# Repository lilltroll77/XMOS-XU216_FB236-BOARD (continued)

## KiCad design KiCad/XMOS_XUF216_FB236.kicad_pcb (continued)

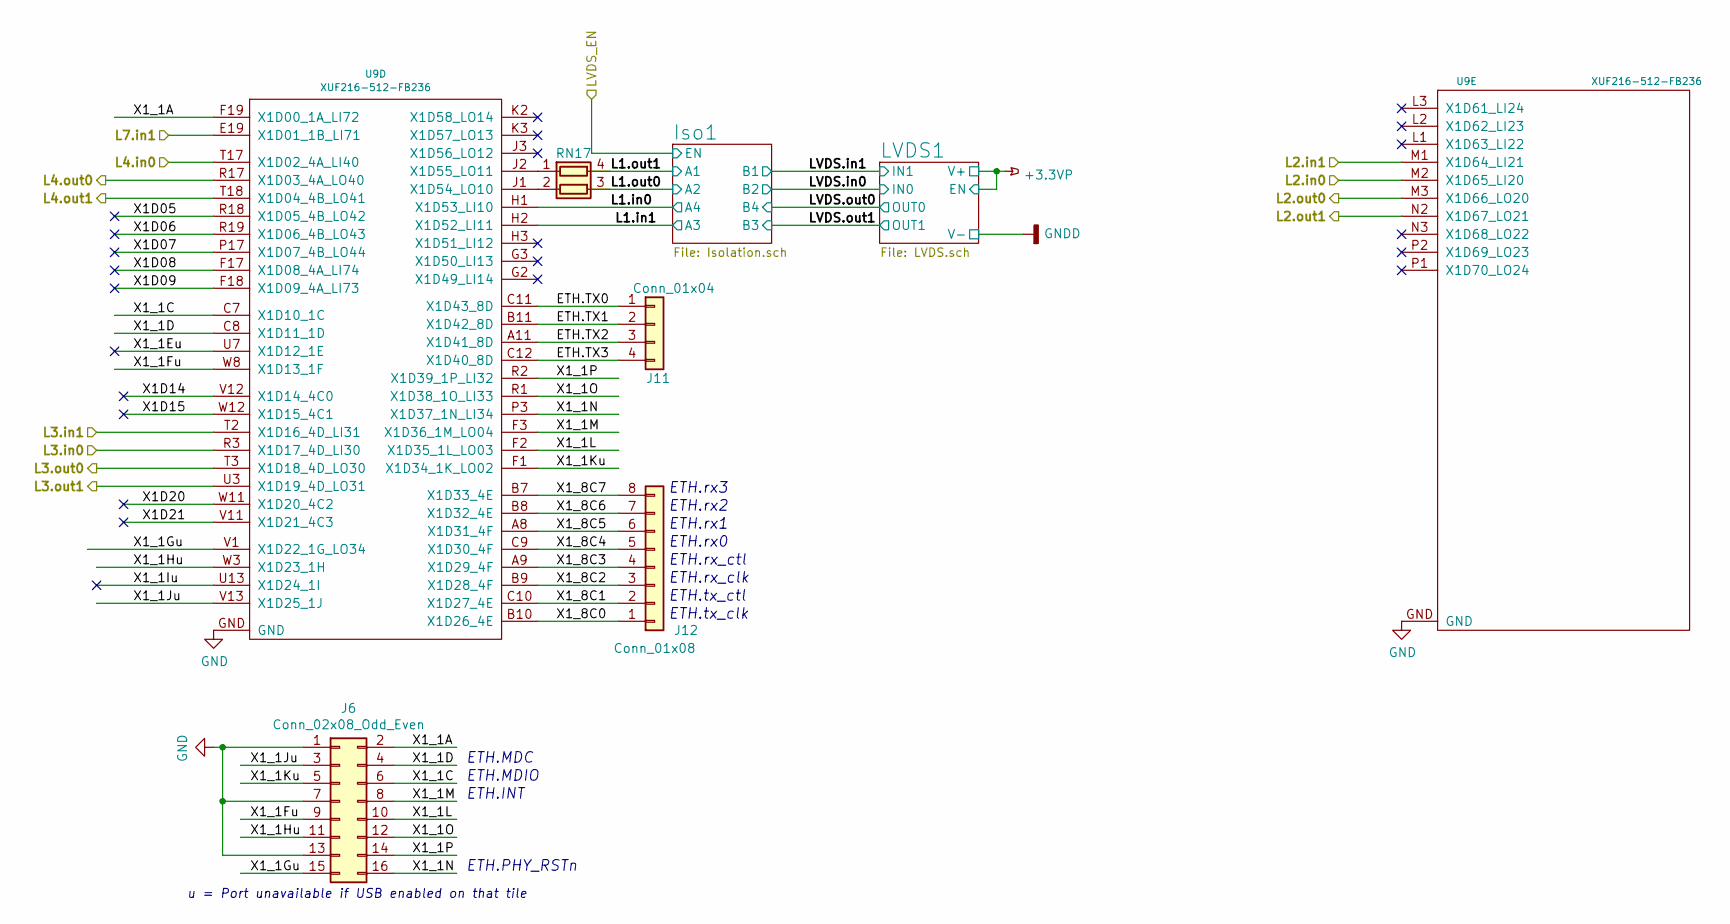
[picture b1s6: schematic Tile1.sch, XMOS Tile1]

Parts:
J6: Conn_02x08_Odd_Even; PinSocket_2x08_P2.54mm_Vertical
J11: Conn_01x04; PinSocket_1x04_P2.54mm_Vertical
J12: Conn_01x08; PinSocket_1x08_P2.54mm_Vertical
RN17: R_Pack02; R_Array_Convex_2x0402
U9: XUF216-512-FB236; BGA_236

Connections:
/L2.in0: U9.M2 (X1D65_LI20); also elsewhere on the board
/L2.in1: U9.M1 (X1D64_LI21); also elsewhere on the board
/L3.in0: U9.R3 (X1D17_4D_LI30); also elsewhere on the board
/L3.in1: U9.T2 (X1D16_4D_LI31); also elsewhere on the board
/L4.in0: U9.T17 (X1D02_4A_LI40); also elsewhere on the board
/L4.out0: U9.R17 (X1D03_4A_LO40); also elsewhere on the board
/L4.out1: U9.T18 (X1D04_4B_LO41); also elsewhere on the board
/L7.in1: U9.E19 (X1D01_1B_LI71); also elsewhere on the board
/Tile1/ETH.TX0: J11.1, U9.C11 (X1D43_8D)
/Tile1/ETH.TX1: J11.2, U9.B11 (X1D42_8D)
/Tile1/ETH.TX2: J11.3, U9.A11 (X1D41_8D)
/Tile1/ETH.TX3: J11.4, U9.C12 (X1D40_8D)
/Tile1/L1.in0: U9.H1 (X1D53_LI10); also elsewhere on the board
/Tile1/L1.in1: U9.H2 (X1D52_LI11); also elsewhere on the board
/Tile1/L1.out0: RN17.3 (R2.2); also elsewhere on the board
/Tile1/L1.out1: RN17.4 (R1.2); also elsewhere on the board
/Tile1/L2.out0: U9.M3 (X1D66_LO20); also elsewhere on the board
/Tile1/L2.out1: U9.N2 (X1D67_LO21); also elsewhere on the board
/Tile1/L3.out0: U9.T3 (X1D18_4D_LO30); also elsewhere on the board
/Tile1/L3.out1: U9.U3 (X1D19_4D_LO31); also elsewhere on the board
/Tile1/X1D05: U9.R18 (X1D05_4B_LO42)
/Tile1/X1D06: U9.R19 (X1D06_4B_LO43)
/Tile1/X1D07: U9.P17 (X1D07_4B_LO44)
/Tile1/X1D08: U9.F17 (X1D08_4A_LI74)
/Tile1/X1D09: U9.F18 (X1D09_4A_LI73)
/Tile1/X1D14: U9.V12 (X1D14_4C0)
/Tile1/X1D15: U9.W12 (X1D15_4C1)
/Tile1/X1D20: U9.W11 (X1D20_4C2)
/Tile1/X1D21: U9.V11 (X1D21_4C3)
/Tile1/X1_1A: J6.2, U9.F19 (X1D00_1A_LI72)
/Tile1/X1_1C: J6.6, U9.C7 (X1D10_1C)
/Tile1/X1_1D: J6.4, U9.C8 (X1D11_1D)
/Tile1/X1_1Eu: U9.U7 (X1D12_1E)
/Tile1/X1_1Fu: J6.9, U9.W8 (X1D13_1F)
/Tile1/X1_1Gu: J6.15, U9.V1 (X1D22_1G_LO34)
/Tile1/X1_1Hu: J6.11, U9.W3 (X1D23_1H)
/Tile1/X1_1Iu: U9.U13 (X1D24_1I)
/Tile1/X1_1Ju: J6.3, U9.V13 (X1D25_1J)
/Tile1/X1_1Ku: J6.5, U9.F1 (X1D34_1K_LO02)
/Tile1/X1_1L: J6.10, U9.F2 (X1D35_1L_LO03)
/Tile1/X1_1M: J6.8, U9.F3 (X1D36_1M_LO04)
/Tile1/X1_1N: J6.16, U9.P3 (X1D37_1N_LI34)
/Tile1/X1_1O: J6.12, U9.R1 (X1D38_1O_LI33)
/Tile1/X1_1P: J6.14, U9.R2 (X1D39_1P_LI32)
/Tile1/X1_8C0: J12.1, U9.B10 (X1D26_4E)
/Tile1/X1_8C1: J12.2, U9.C10 (X1D27_4E)
/Tile1/X1_8C2: J12.3, U9.B9 (X1D28_4F)
/Tile1/X1_8C3: J12.4, U9.A9 (X1D29_4F)
/Tile1/X1_8C4: J12.5, U9.C9 (X1D30_4F)
/Tile1/X1_8C5: J12.6, U9.A8 (X1D31_4F)
/Tile1/X1_8C6: J12.7, U9.B8 (X1D32_4E)
/Tile1/X1_8C7: J12.8, U9.B7 (X1D33_4E)
GND: J6.1, J6.7, J6.13, U9.GND; also elsewhere on the board
unnamed: RN17.1 (R1.1), U9.J2 (X1D55_LO11)
unnamed: RN17.2 (R2.1), U9.J1 (X1D54_LO10)

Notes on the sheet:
u = Port unavailable if USB enabled on that tile
ETH.MDIO
ETH.MDC
ETH.INT
ETH.PHY_RSTn
ETH.rx3
ETH.rx2
ETH.rx1
ETH.rx0
ETH.rx_ctl
ETH.rx_clk
ETH.tx_ctl
ETH.tx_clk

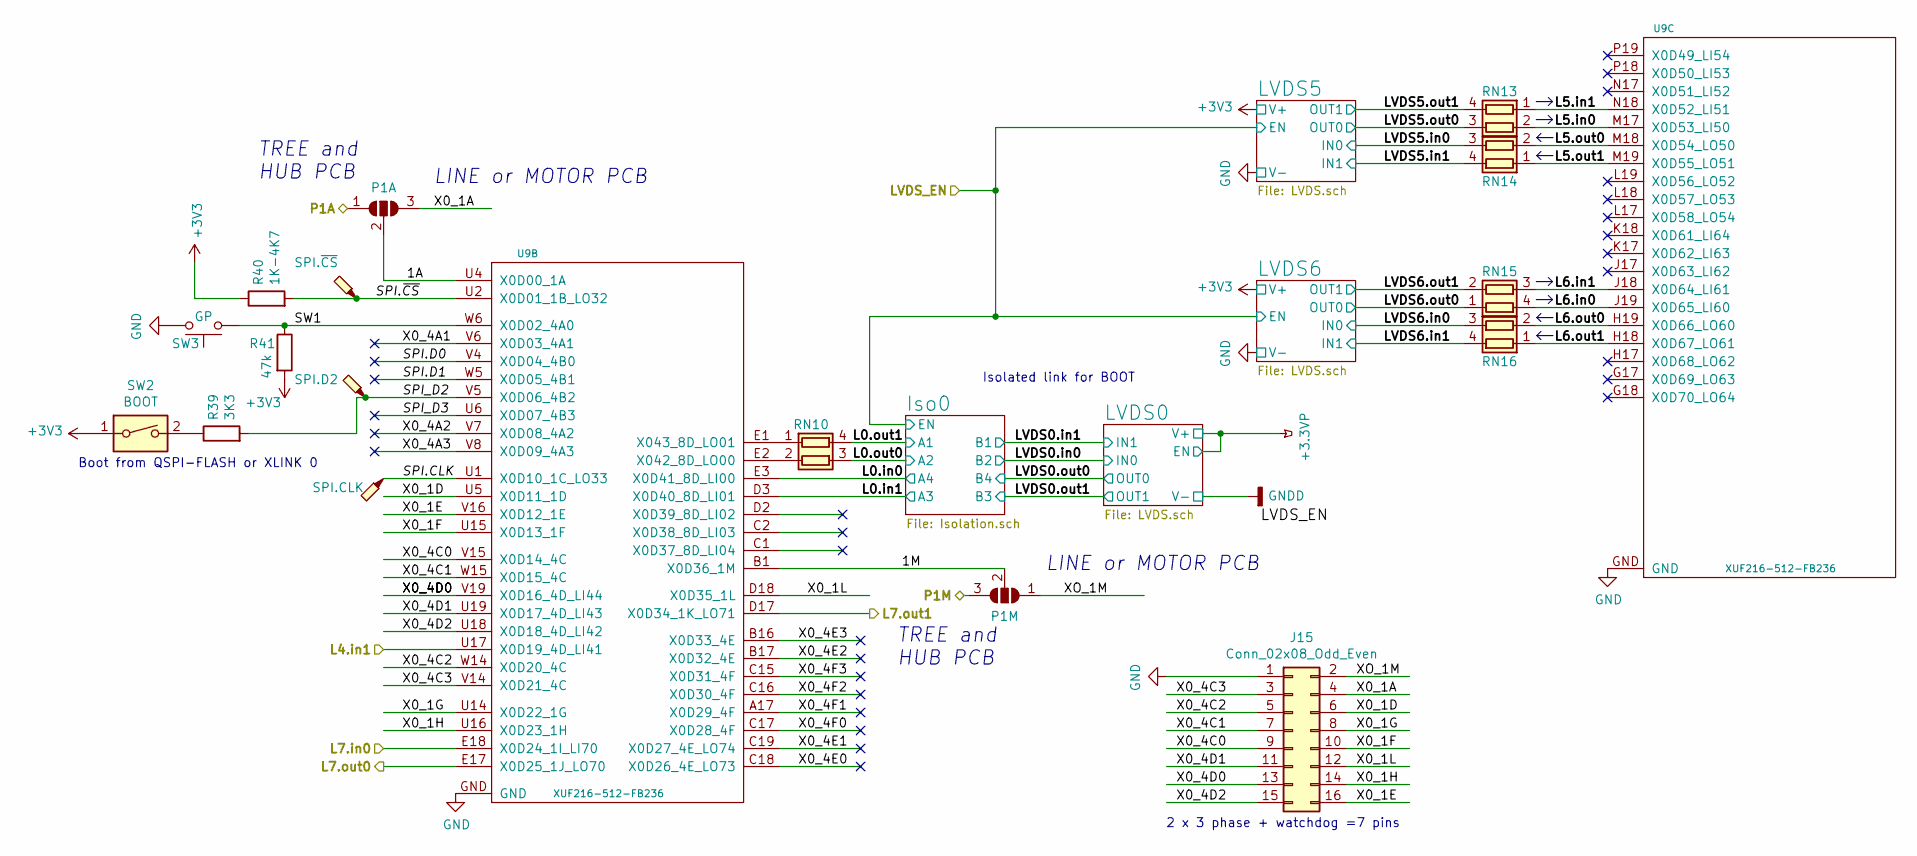
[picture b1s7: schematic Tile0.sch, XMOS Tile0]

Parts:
J15: Conn_02x08_Odd_Even; PinSocket_2x08_P2.54mm_Vertical
JP18: P1A; SolderJumper-3_P1.3mm_Open_RoundedPad1.0x1.5mm_NumberLabels
JP19: P1M; SolderJumper-3_P1.3mm_Open_RoundedPad1.0x1.5mm_NumberLabels
R39: 3K3; R_0603_1608Metric_Pad1.05x0.95mm_HandSolder
R40: 1K-4K7; R_0603_1608Metric_Pad1.05x0.95mm_HandSolder
R41: 47k; R_0603_1608Metric_Pad1.05x0.95mm_HandSolder
RN10, RN13, RN14, RN15, RN16: R_Pack02; R_Array_Convex_2x0402
SW2: BOOT; SW_DIP_SPSTx01_Slide_6.7x4.1mm_W6.73mm_P2.54mm_LowProfile_J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
SW3: GP; SW_SPST_B3U-1000P
TP20: SPI.~CS; TestPoint_Pad_0.6x0.6mm
TP21: SPI.D2; TestPoint_Pad_0.6x0.6mm
TP22: SPI.CLK; TestPoint_Pad_0.6x0.6mm
U9: XUF216-512-FB236; BGA_236

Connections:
/L4.in1: U9.U17 (X0D19_4D_LI41); also elsewhere on the board
/L7.in0: U9.E18 (X0D24_1I_LI70); also elsewhere on the board
/L7.out0: U9.E17 (X0D25_1J_LO70); also elsewhere on the board
/L7.out1: U9.D17 (X0D34_1K_LO71); also elsewhere on the board
/Tile0/1A: JP18.2 (C), U9.U4 (X0D00_1A)
/Tile0/1M: JP19.2 (C), U9.B1 (X0D36_1M)
/Tile0/L0.in0: U9.E3 (X0D41_8D_LI00); also elsewhere on the board
/Tile0/L0.in1: U9.D3 (X0D40_8D_LI01); also elsewhere on the board
/Tile0/L0.out0: RN10.3 (R2.2); also elsewhere on the board
/Tile0/L0.out1: RN10.4 (R1.2); also elsewhere on the board
/Tile0/L5.in0: RN13.2 (R2.1), U9.M17 (X0D53_LI50)
/Tile0/L5.in1: RN13.1 (R1.1), U9.N18 (X0D52_LI51)
/Tile0/L5.out0: RN14.2 (R2.1), U9.M18 (X0D54_LO50)
/Tile0/L5.out1: RN14.1 (R1.1), U9.M19 (X0D55_LO51)
/Tile0/L6.in0: RN15.4 (R1.2), U9.J19 (X0D65_LI60)
/Tile0/L6.in1: RN15.3 (R2.2), U9.J18 (X0D64_LI61)
/Tile0/L6.out0: RN16.2 (R2.1), U9.H19 (X0D66_LO60)
/Tile0/L6.out1: RN16.1 (R1.1), U9.H18 (X0D67_LO61)
/Tile0/LVDS5.in0: RN14.3 (R2.2); also elsewhere on the board
/Tile0/LVDS5.in1: RN14.4 (R1.2); also elsewhere on the board
/Tile0/LVDS5.out0: RN13.3 (R2.2); also elsewhere on the board
/Tile0/LVDS5.out1: RN13.4 (R1.2); also elsewhere on the board
/Tile0/LVDS6.in0: RN16.3 (R2.2); also elsewhere on the board
/Tile0/LVDS6.in1: RN16.4 (R1.2); also elsewhere on the board
/Tile0/LVDS6.out0: RN15.1 (R1.1); also elsewhere on the board
/Tile0/LVDS6.out1: RN15.2 (R2.1); also elsewhere on the board
/Tile0/SPI.CLK: TP22.1, U9.U1 (X0D10_1C_LO33)
/Tile0/SPI.D0: U9.V4 (X0D04_4B0)
/Tile0/SPI.D1: U9.W5 (X0D05_4B1)
/Tile0/SPI.~CS: R40.2, TP20.1, U9.U2 (X0D01_1B_LO32)
/Tile0/SPI_D2: R39.2, TP21.1, U9.V5 (X0D06_4B2)
/Tile0/SPI_D3: U9.U6 (X0D07_4B3)
/Tile0/SW1: R41.1, SW3.1, U9.W6 (X0D02_4A0)
/Tile0/X0_1A: J15.4, JP18.3 (B)
/Tile0/X0_1D: J15.6, U9.U5 (X0D11_1D)
/Tile0/X0_1E: J15.16, U9.V16 (X0D12_1E)
/Tile0/X0_1F: J15.10, U9.U15 (X0D13_1F)
/Tile0/X0_1G: J15.8, U9.U14 (X0D22_1G)
/Tile0/X0_1H: J15.14, U9.U16 (X0D23_1H)
/Tile0/X0_1L: J15.12, U9.D18 (X0D35_1L)
/Tile0/X0_4A1: U9.V6 (X0D03_4A1)
/Tile0/X0_4A2: U9.V7 (X0D08_4A2)
/Tile0/X0_4A3: U9.V8 (X0D09_4A3)
/Tile0/X0_4C0: J15.9, U9.V15 (X0D14_4C)
/Tile0/X0_4C1: J15.7, U9.W15 (X0D15_4C)
/Tile0/X0_4C2: J15.5, U9.W14 (X0D20_4C)
/Tile0/X0_4C3: J15.3, U9.V14 (X0D21_4C)
/Tile0/X0_4D0: J15.13, U9.V19 (X0D16_4D_LI44)
/Tile0/X0_4D1: J15.11, U9.U19 (X0D17_4D_LI43)
/Tile0/X0_4D2: J15.15, U9.U18 (X0D18_4D_LI42)
/Tile0/X0_4E0: U9.C18 (X0D26_4E_LO73)
/Tile0/X0_4E1: U9.C19 (X0D27_4E_LO74)
/Tile0/X0_4E2: U9.B17 (X0D32_4E)
/Tile0/X0_4E3: U9.B16 (X0D33_4E)
/Tile0/X0_4F0: U9.C17 (X0D28_4F)
/Tile0/X0_4F1: U9.A17 (X0D29_4F)
/Tile0/X0_4F2: U9.C16 (X0D30_4F)
/Tile0/X0_4F3: U9.C15 (X0D31_4F)
/Tile0/XO_1M: J15.2, JP19.1 (A)
/UART.RX: JP18.1 (A); also elsewhere on the board
/UART.TX: JP19.3 (B); also elsewhere on the board
GND: J15.1, SW3.2, U9.GND; also elsewhere on the board
unnamed: R39.1, SW2.2
unnamed: RN10.1 (R1.1), U9.E1 (X043_8D_LO01)
unnamed: RN10.2 (R2.1), U9.E2 (X042_8D_LO00)

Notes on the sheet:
2 x 3 phase + watchdog =7 pins
Boot from QSPI-FLASH or XLINK 0
Isolated link for BOOT
TREE and HUB PCB
LINE or MOTOR PCB

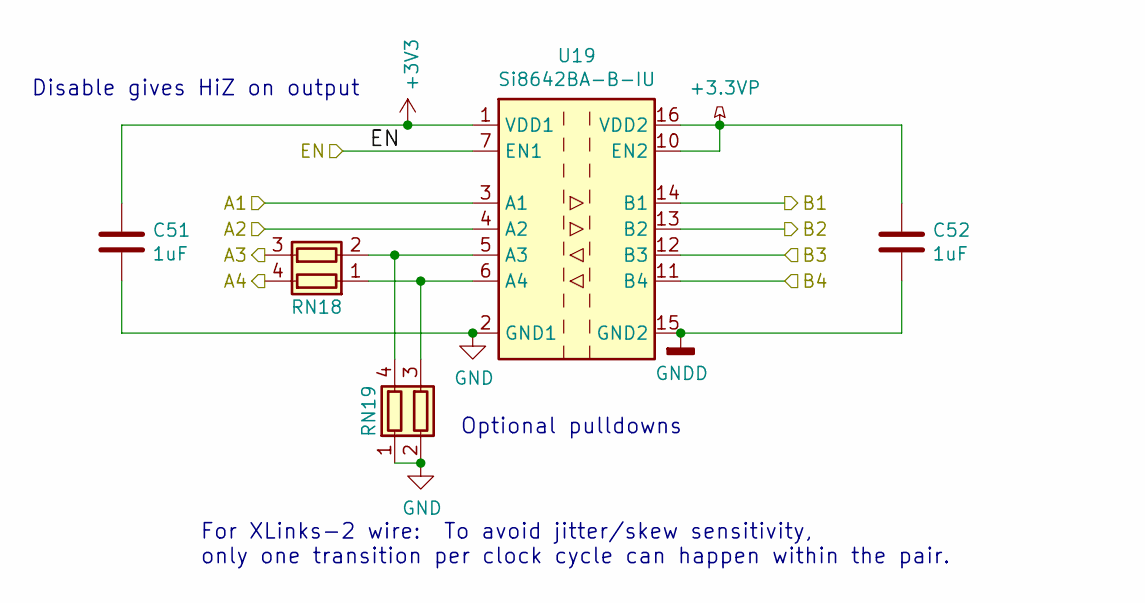
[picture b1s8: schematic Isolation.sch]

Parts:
C51, C52: 1uF; C_0603_1608Metric_Pad1.05x0.95mm_HandSolder
RN18, RN19: R_Pack02; R_Array_Convex_2x0402
U19: Si8642BA-B-IU; QSOP-16_3.9x4.9mm_P0.635mm

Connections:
+3.3VP: C52.1, U19.10 (EN2), U19.16 (VDD2); also elsewhere on the board
/LVDS_EN: U19.7 (EN1); also elsewhere on the board
/Tile0/L0.in0: RN18.4 (R1.2); also elsewhere on the board
/Tile0/L0.in1: RN18.3 (R2.2); also elsewhere on the board
/Tile0/L0.out0: U19.4 (A2); also elsewhere on the board
/Tile0/L0.out1: U19.3 (A1); also elsewhere on the board
/Tile0/LVDS0.in0: U19.13 (B2); also elsewhere on the board
/Tile0/LVDS0.in1: U19.14 (B1); also elsewhere on the board
/Tile0/LVDS0.out0: U19.11 (B4); also elsewhere on the board
/Tile0/LVDS0.out1: U19.12 (B3); also elsewhere on the board
GND: C51.2, RN19.1 (R1.1), RN19.2 (R2.1), U19.2 (GND1), U19.8 (GND1); also elsewhere on the board
GNDD: C52.2, U19.9 (GND2), U19.15 (GND2); also elsewhere on the board
unnamed: RN18.1 (R1.1), RN19.3 (R2.2), U19.6 (A4)
unnamed: RN18.2 (R2.1), RN19.4 (R1.2), U19.5 (A3)

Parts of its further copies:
C44, C45: 1uF; C_0603_1608Metric_Pad1.05x0.95mm_HandSolder
RN11, RN12: R_Pack02; R_Array_Convex_2x0402
U13: Si8642BA-B-IU; QSOP-16_3.9x4.9mm_P0.635mm

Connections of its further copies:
+3.3VP: C45.1, U13.10 (EN2), U13.16 (VDD2); also elsewhere on the board
/LVDS_EN: U13.7 (EN1); also elsewhere on the board
/Tile1/L1.in0: RN11.4 (R1.2); also elsewhere on the board
/Tile1/L1.in1: RN11.3 (R2.2); also elsewhere on the board
/Tile1/L1.out0: U13.4 (A2); also elsewhere on the board
/Tile1/L1.out1: U13.3 (A1); also elsewhere on the board
/Tile1/LVDS.in0: U13.13 (B2); also elsewhere on the board
/Tile1/LVDS.in1: U13.14 (B1); also elsewhere on the board
/Tile1/LVDS.out0: U13.11 (B4); also elsewhere on the board
/Tile1/LVDS.out1: U13.12 (B3); also elsewhere on the board
GND: C44.2, RN12.1 (R1.1), RN12.2 (R2.1), U13.2 (GND1), U13.8 (GND1); also elsewhere on the board
GNDD: C45.2, U13.9 (GND2), U13.15 (GND2); also elsewhere on the board
unnamed: RN11.1 (R1.1), RN12.3 (R2.2), U13.6 (A4)
unnamed: RN11.2 (R2.1), RN12.4 (R1.2), U13.5 (A3)

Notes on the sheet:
For XLinks-2 wire: To avoid jitter/skew sensitivity, only one transition per clock cycle can happen within the pair.
Disable gives HiZ on output
Optional pulldowns

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
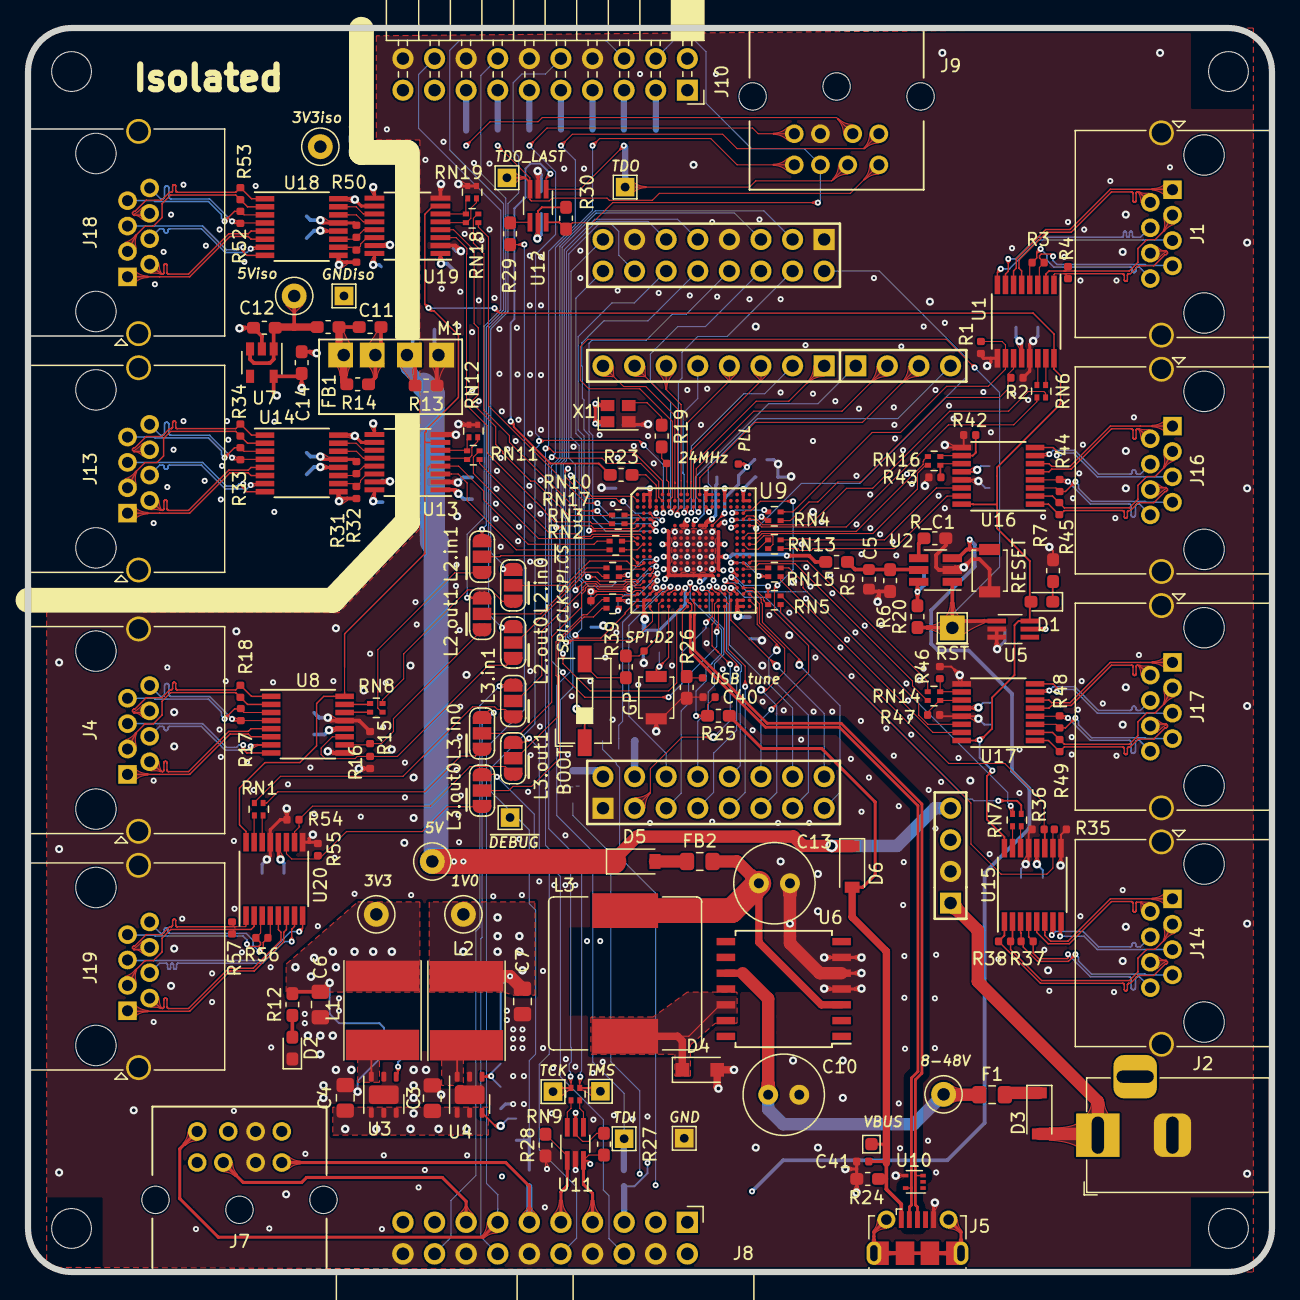
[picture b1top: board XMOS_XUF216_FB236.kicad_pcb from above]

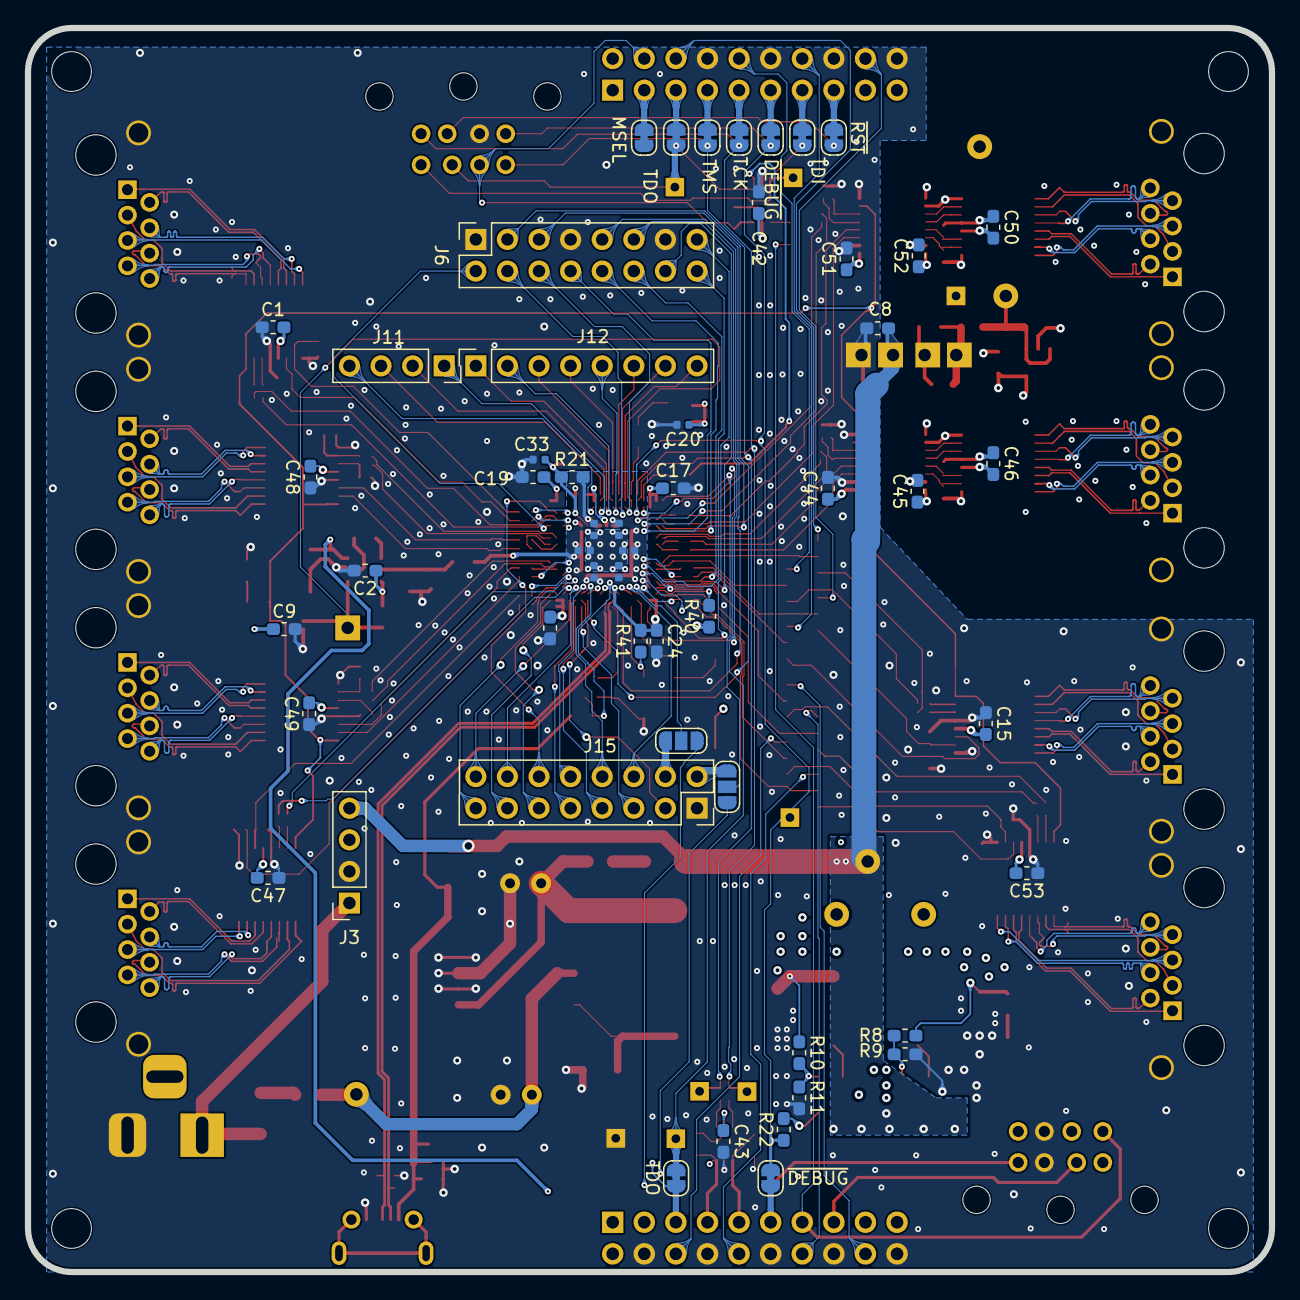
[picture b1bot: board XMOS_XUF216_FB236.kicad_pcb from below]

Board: 4 copper layers, 100.0 x 100.0 mm, 219 parts (53 on the bottom side), 258 nets.

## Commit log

2018-12-29 Added a set of termination resistors
2018-12-29 Changed plotmode of Board.pdf
2018-12-29 Updated Fab Layer in board
2018-12-30 Added reference pdf and some schematic fixes.
2018-12-30 Added LVDS enable and small fixes
2018-12-30 Added RJ45 picture
2018-12-30 Added more No connect flags and changed colors
2018-12-30 Added powerpoints
2018-12-31 Changed Xlink and XTAG labels to dot notation
2018-12-31 Added testpoints
2018-12-31 Some small fixes
2019-01-01 Added network definitions for XMOS
2019-01-01 Simulated networks
2019-01-01 Added Mini DIN8 connectors and TREE/LINE choice
2019-01-01 Schematic refactoring
2019-01-03 Added new board renderings and small schematic adjustment
2019-01-03 Updated board and renders
2019-01-03 Minor changes to the PCB
2019-01-04 Added VR files
2019-01-04 Added M3 standoffs
2019-01-04 Changed DC jack to pj-202bh
2019-01-04 Added BGA mask alternative
2019-01-05 Added KiCAD files
2019-01-06 Added impedance calc, and rerouted USB
2019-01-08 Many small fixes
2019-01-08 Updated VRML and schematic
2020-06-17 Update
    Updated to KiCad 5.1.6 and changed the power sheet etc.
